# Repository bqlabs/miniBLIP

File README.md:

# miniBLIP
### miniBLIP
Prototyping Board developed together with @Victornomad for @Circolab friends.

A new way of approaching electronics, complete and cost effective!

### License
This project is licensed under [CC-BY-SA](http://creativecommons.org/licenses/by-sa/3.0/es/)

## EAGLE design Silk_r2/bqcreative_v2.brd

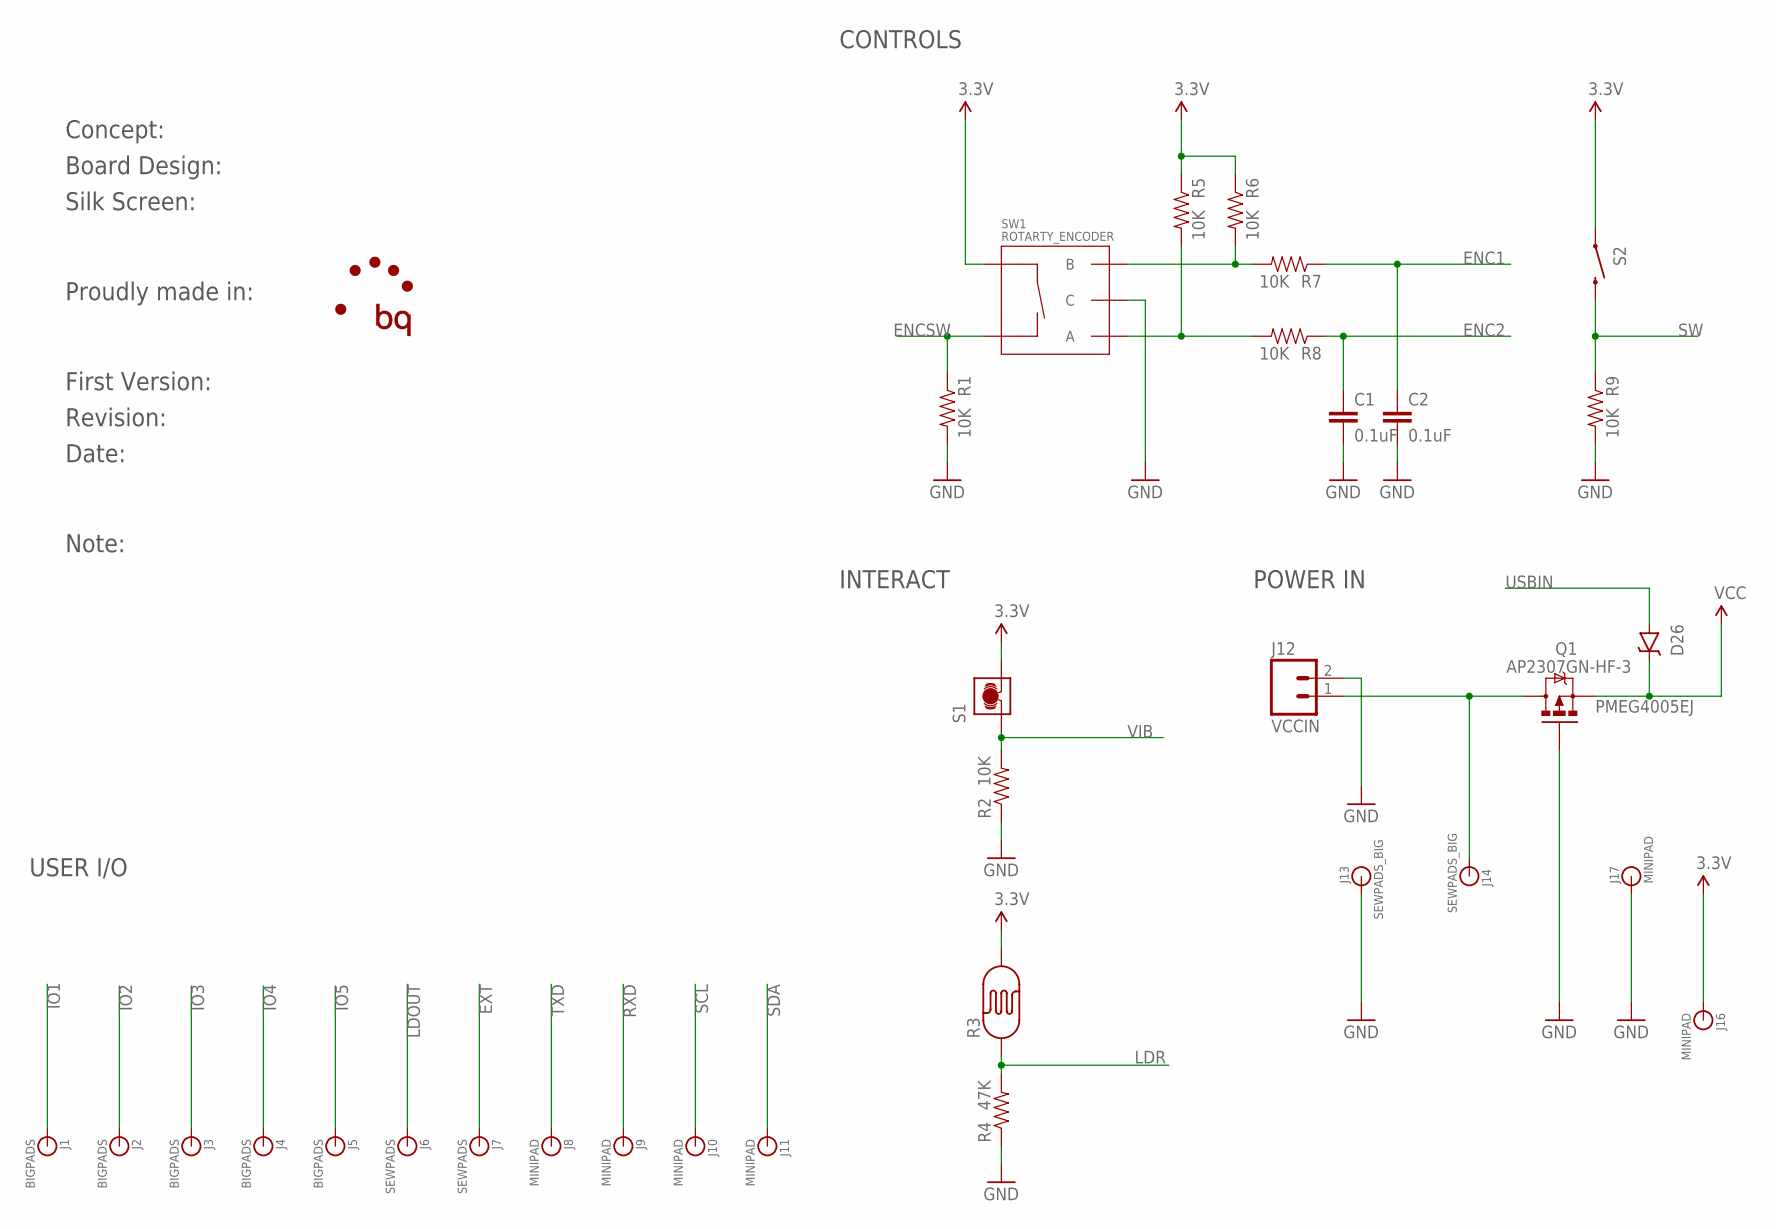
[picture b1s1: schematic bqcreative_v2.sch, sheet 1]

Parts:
C1, C2: 0.1uF; 0603-CAP
D26: PMEG4005EJ; SOD-323
J1, J2, J3, J4, J5: BIGPADS; BIGPAD
J6, J7: SEWPADS; SEWPAD
J8, J9, J10, J11, J16, J17: MINIPAD
J12: VCCIN; MOLEX-1X2
J13, J14: SEWPADS_BIG; SEWPAD_BIG
Q1: AP2307GN-HF-3; SOT23-3
R1, R2, R5, R6, R7, R8, R9: 10K; 0402-RES
R3: PHOTOCELLPTH; PHOTOCELL
R4: 47K; 0402-RES
S1: VIBRATION-SWITCH
S2: SWITCH-MOMENTARY-2SMD; TACTILE-SWITCH-SMD
SW1: ROTARTY_ENCODER; ROTARY_ENC_PLAIN

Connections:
3.3V: J16.P$1, J16.P$2, R3.2, R5.1, R6.1, S1.2, S2.1, SW1.SW+; also elsewhere on the board
ENC1: C2.1, R7.1; also elsewhere on the board
ENC2: C1.1, R8.1; also elsewhere on the board
ENCSW: R1.1, SW1.SW-; also elsewhere on the board
EXT: J7.P$1; also elsewhere on the board
GND: C1.2, C2.2, J12.2, J13.P$1, J17.P$1, J17.P$2, Q1.1 (G), R1.2, R2.1, R4.1, R9.2, SW1.C; also elsewhere on the board
IO1: J1.P$1; also elsewhere on the board
IO2: J2.P$1; also elsewhere on the board
IO3: J3.P$1; also elsewhere on the board
IO4: J4.P$1; also elsewhere on the board
IO5: J5.P$1; also elsewhere on the board
LDOUT: J6.P$1; also elsewhere on the board
LDR: R3.1, R4.2; also elsewhere on the board
unnamed: J12.1, J14.P$1, Q1.3 (D)
unnamed: R6.2, R7.2, SW1.B
unnamed: R5.2, R8.2, SW1.A
RXD: J9.P$1, J9.P$2; also elsewhere on the board
SCL: J10.P$1, J10.P$2; also elsewhere on the board
SDA: J11.P$1, J11.P$2; also elsewhere on the board
SW: R9.1, S2.3 (2); also elsewhere on the board
TXD: J8.P$1, J8.P$2; also elsewhere on the board
USBIN: D26.A; also elsewhere on the board
VCC: D26.C, Q1.2 (S); also elsewhere on the board
VIB: R2.2, S1.1; also elsewhere on the board

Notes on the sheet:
CONTROLS
USER I/O
INTERACT
POWER IN
Concept:
Board Design:
Silk Screen:
Proudly made in:
First Version:
Revision:
Date:
Note:

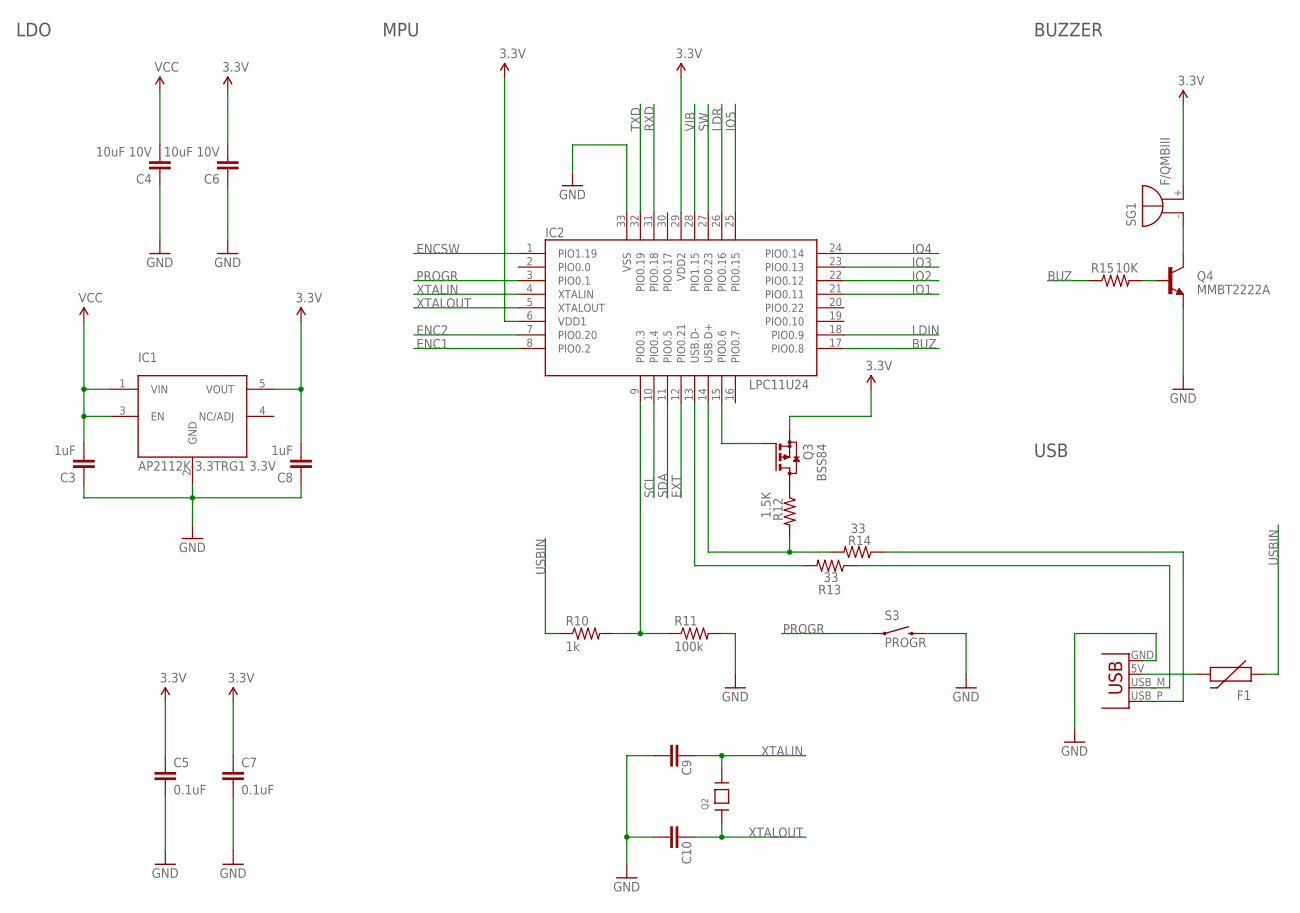
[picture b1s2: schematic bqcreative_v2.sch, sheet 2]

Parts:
C3, C8: 1uF; 0402-CAP
C4, C6: 10uF 10V; 0402-CAP
C5, C7: 0.1uF; 0402-CAP
C9, C10: 27pF; 0402-CAP
F1: PTC0603; 0603
IC1: AP2112K-3.3TRG1 3.3V; SOT23-5
IC2: LPC11U24; HVQFN33_5X5MM
J15: USBPCB; USB-A-PCB
Q2: 12MHz 4 pad crystal 3.2x2.5; CRYSTAL_3.2X2.5
Q3: BSS84; SOT23
Q4: MMBT2222A; SOT23-3
R10: 1k; 0402-RES
R11: 100k; 0402-RES
R12: 1.5K; 0402-RES
R13, R14: 33; 0402-RES
R15: 10K; 0402-RES
S3: PROGR; TACTILE-SWITCH-1101NE
SG1: F/QMBIII

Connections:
3.3V: C5.1, C6.2, C7.1, C8.2, IC1.5 (VOUT), IC2.6 (VDD1), IC2.29 (VDD2), Q3.2 (S), SG1.+ (-); also elsewhere on the board
BUZ: IC2.17 (PIO0.8), R15.1
ENC1: IC2.8 (PIO0.2); also elsewhere on the board
ENC2: IC2.7 (PIO0.20); also elsewhere on the board
ENCSW: IC2.1 (PIO1.19); also elsewhere on the board
EXT: IC2.12 (PIO0.21); also elsewhere on the board
GND: C3.1, C4.1, C5.2, C6.1, C7.2, C8.1, C9.2, C10.2, IC1.2 (GND), IC2.33 (VSS), J15.GND, Q4.2 (E), R11.2, S3.2; also elsewhere on the board
IO1: IC2.21 (PIO0.11); also elsewhere on the board
IO2: IC2.22 (PIO0.12); also elsewhere on the board
IO3: IC2.23 (PIO0.13); also elsewhere on the board
IO4: IC2.24 (PIO0.14); also elsewhere on the board
IO5: IC2.25 (PIO0.15); also elsewhere on the board
LDIN: IC2.18 (PIO0.9); also elsewhere on the board
LDR: IC2.26 (PIO0.16); also elsewhere on the board
unnamed: Q4.3 (C), SG1.- (+)
unnamed: Q4.1 (B), R15.2
unnamed: J15.USB_P (D+), R14.1
unnamed: F1.2, J15.5V (VBUS)
unnamed: J15.USB_M (D-), R13.1
unnamed: IC2.14 (USB.D+), R12.2, R14.2
unnamed: IC2.13 (USB.D-), R13.2
unnamed: Q3.3 (D), R12.1
unnamed: IC2.15 (PIO0.6), Q3.1 (G)
P0.3/ISP_COMMAND_USB_HIGH: IC2.9 (PIO0.3), R10.2, R11.1
PROGR: IC2.3 (PIO0.1), S3.1
RXD: IC2.31 (PIO0.18); also elsewhere on the board
SCL: IC2.10 (PIO0.4); also elsewhere on the board
SDA: IC2.11 (PIO0.5); also elsewhere on the board
SW: IC2.27 (PIO0.23); also elsewhere on the board
TXD: IC2.32 (PIO0.19); also elsewhere on the board
USBIN: F1.1, R10.1; also elsewhere on the board
VCC: C3.2, C4.2, IC1.1 (VIN), IC1.3 (EN); also elsewhere on the board
VIB: IC2.28 (PIO1.15); also elsewhere on the board
XTALIN: C9.1, IC2.4 (XTALIN), Q2.3
XTALOUT: C10.1, IC2.5 (XTALOUT), Q2.1

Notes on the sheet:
LDO
MPU
BUZZER
USB

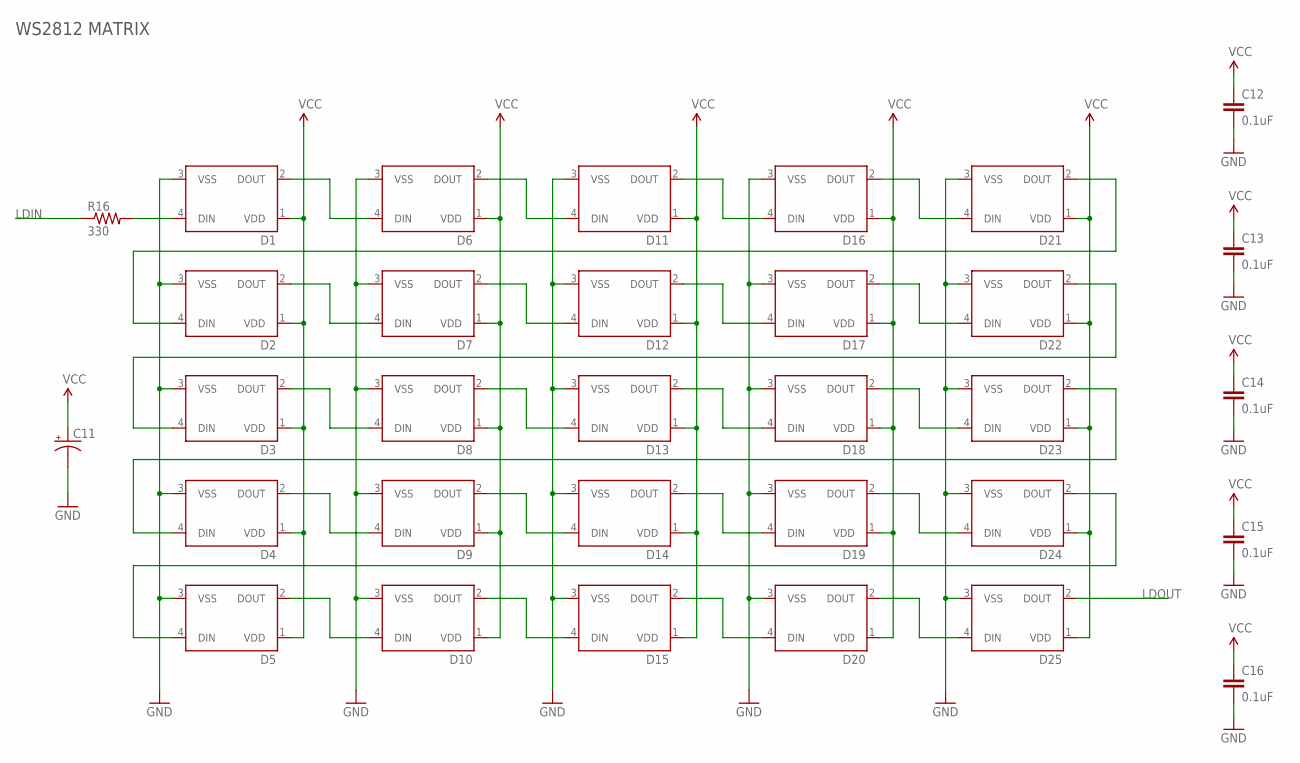
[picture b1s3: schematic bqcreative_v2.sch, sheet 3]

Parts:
C11: CAP_POL1206; EIA3216
C12, C13, C14, C15, C16: 0.1uF; 0402-CAP
D1, D2, D3, D4, D5, D6, D7, D8, D9, D10, D11, D12, D13, D14, D15, D16, D17, D18, D19, D20, D21, D22, D23, D24, D25: WS2812B
R16: 330; 0402-RES

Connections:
GND: C11.C (-), C12.2, C13.2, C14.2, C15.2, C16.2, D1.3 (VSS), D2.3 (VSS), D3.3 (VSS), D4.3 (VSS), D5.3 (VSS), D6.3 (VSS), D7.3 (VSS), D8.3 (VSS), D9.3 (VSS), D10.3 (VSS), D11.3 (VSS), D12.3 (VSS), D13.3 (VSS), D14.3 (VSS), D15.3 (VSS), D16.3 (VSS), D17.3 (VSS), D18.3 (VSS), D19.3 (VSS), D20.3 (VSS), D21.3 (VSS), D22.3 (VSS), D23.3 (VSS), D24.3 (VSS), D25.3 (VSS); also elsewhere on the board
LDIN: R16.1; also elsewhere on the board
LDOUT: D25.2 (DOUT); also elsewhere on the board
unnamed: D1.4 (DIN), R16.2
unnamed: D1.2 (DOUT), D6.4 (DIN)
unnamed: D6.2 (DOUT), D11.4 (DIN)
unnamed: D11.2 (DOUT), D16.4 (DIN)
unnamed: D16.2 (DOUT), D21.4 (DIN)
unnamed: D2.2 (DOUT), D7.4 (DIN)
unnamed: D7.2 (DOUT), D12.4 (DIN)
unnamed: D12.2 (DOUT), D17.4 (DIN)
unnamed: D17.2 (DOUT), D22.4 (DIN)
unnamed: D3.2 (DOUT), D8.4 (DIN)
unnamed: D8.2 (DOUT), D13.4 (DIN)
unnamed: D13.2 (DOUT), D18.4 (DIN)
unnamed: D18.2 (DOUT), D23.4 (DIN)
unnamed: D4.2 (DOUT), D9.4 (DIN)
unnamed: D9.2 (DOUT), D14.4 (DIN)
unnamed: D14.2 (DOUT), D19.4 (DIN)
unnamed: D19.2 (DOUT), D24.4 (DIN)
unnamed: D5.2 (DOUT), D10.4 (DIN)
unnamed: D10.2 (DOUT), D15.4 (DIN)
unnamed: D15.2 (DOUT), D20.4 (DIN)
unnamed: D20.2 (DOUT), D25.4 (DIN)
unnamed: D2.4 (DIN), D21.2 (DOUT)
unnamed: D3.4 (DIN), D22.2 (DOUT)
unnamed: D4.4 (DIN), D23.2 (DOUT)
unnamed: D5.4 (DIN), D24.2 (DOUT)
VCC: C11.A (+), C12.1, C13.1, C14.1, C15.1, C16.1, D1.1 (VDD), D2.1 (VDD), D3.1 (VDD), D4.1 (VDD), D5.1 (VDD), D6.1 (VDD), D7.1 (VDD), D8.1 (VDD), D9.1 (VDD), D10.1 (VDD), D11.1 (VDD), D12.1 (VDD), D13.1 (VDD), D14.1 (VDD), D15.1 (VDD), D16.1 (VDD), D17.1 (VDD), D18.1 (VDD), D19.1 (VDD), D20.1 (VDD), D21.1 (VDD), D22.1 (VDD), D23.1 (VDD), D24.1 (VDD), D25.1 (VDD); also elsewhere on the board

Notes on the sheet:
WS2812 MATRIX

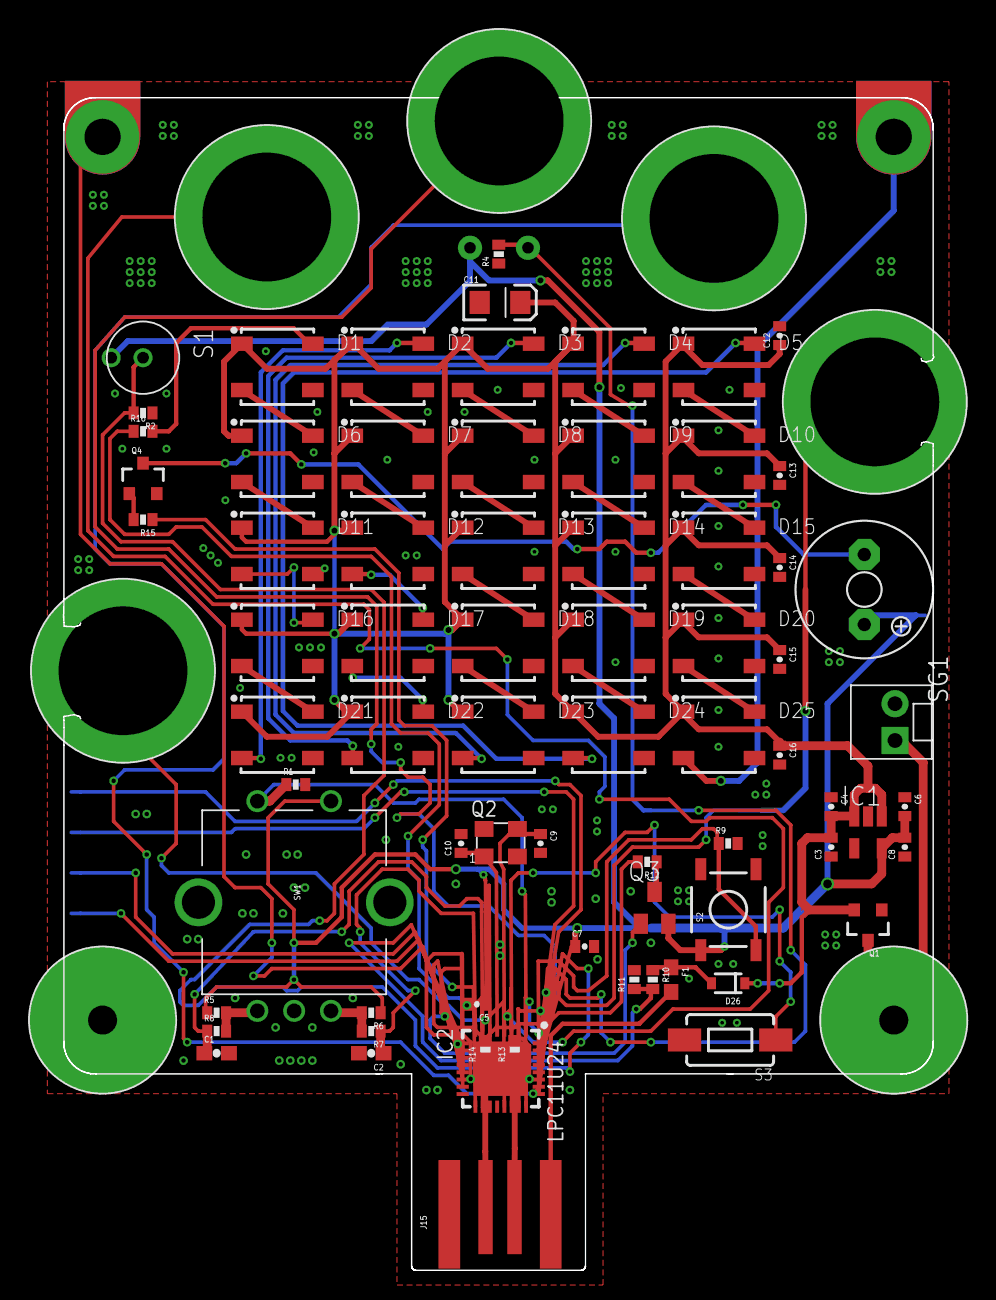
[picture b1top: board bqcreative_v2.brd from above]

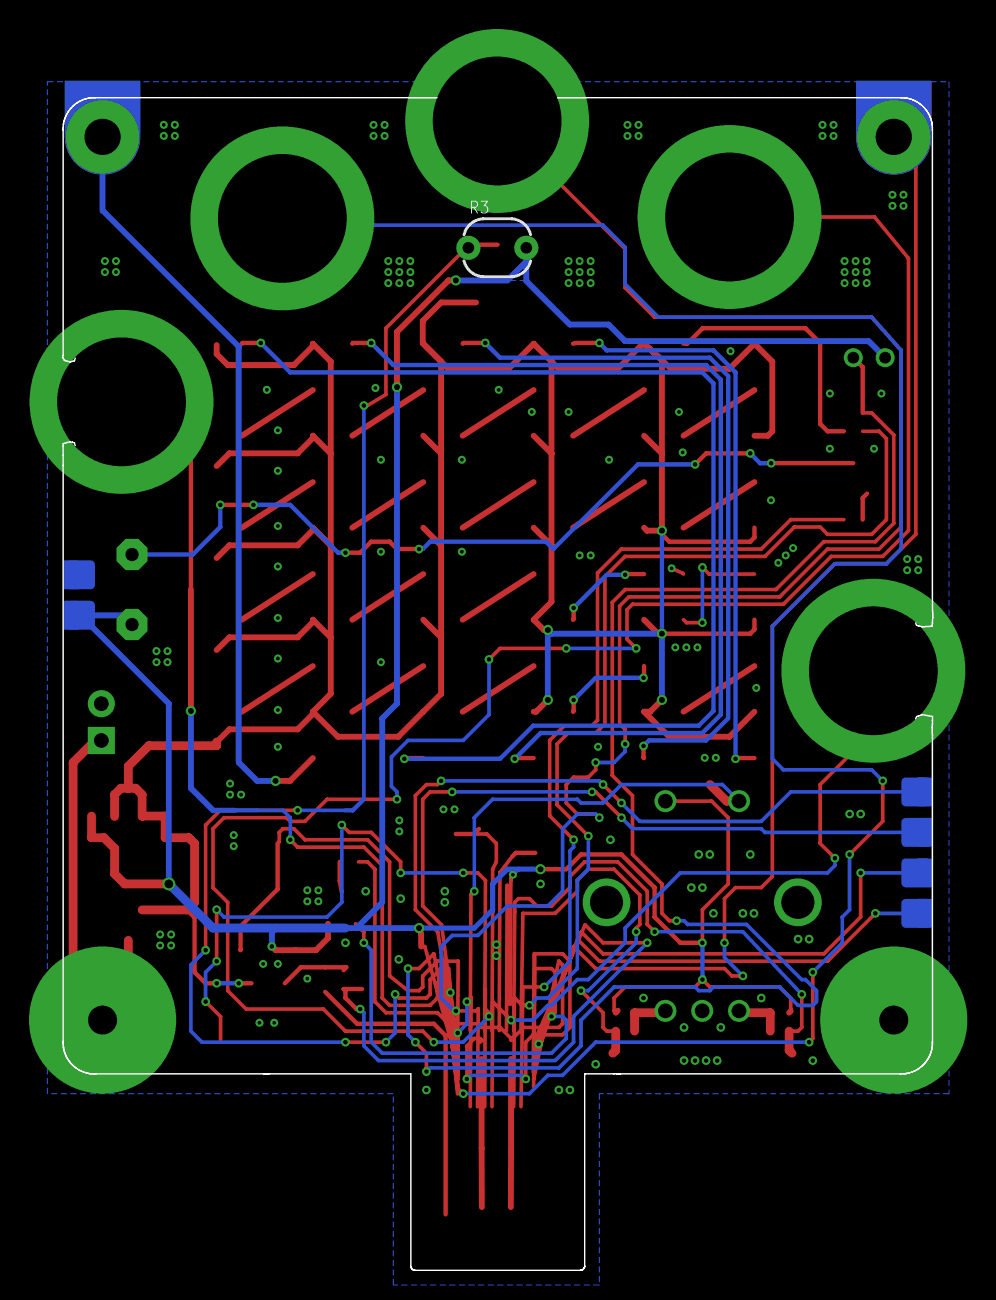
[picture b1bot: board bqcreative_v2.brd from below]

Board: 2 copper layers, 60.1 x 80.9 mm, 89 parts (7 on the bottom side), 64 nets.

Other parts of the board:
U$1: CIRCOLAB_LOGO
U$2: CIRCOLAB_BQ_LOGO

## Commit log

2015-11-30 loader&pinout
    Added loader source & pinout
2015-12-04 Adding license #2
2016-03-11 Add main image and tags

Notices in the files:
parts and their libraries:
SparkFun-Passives: Licensing: Creative Commons ShareAlike 4.0 International - https://creativecommons.org/licenses/by-sa/4.0
SparkFun-PowerIC: Licensing: CC v3.0 Share-Alike You are welcome to use this library for commercial purposes.
